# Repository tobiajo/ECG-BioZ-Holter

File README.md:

# ECG/BioZ Holter (c) by Tobias Johansson

Design and development of a pocket-sized ECG device with respiration monitoring, accelerometer and gyroscope. The produced prototype transmits sampled data with a MCU (PIC24) over Bluetooth to an Android device for which a simple app was developed. To achieve the objective; a system solution was engineered, components chose, PCB designed, soldering done and components programmed or configured.

## Main components

- Texas Instruments ADS1292R
- InvenSense MPU-6050
- Microchip PIC24FJ64GA002
- HC-05 Bluetooth Module

## System overview

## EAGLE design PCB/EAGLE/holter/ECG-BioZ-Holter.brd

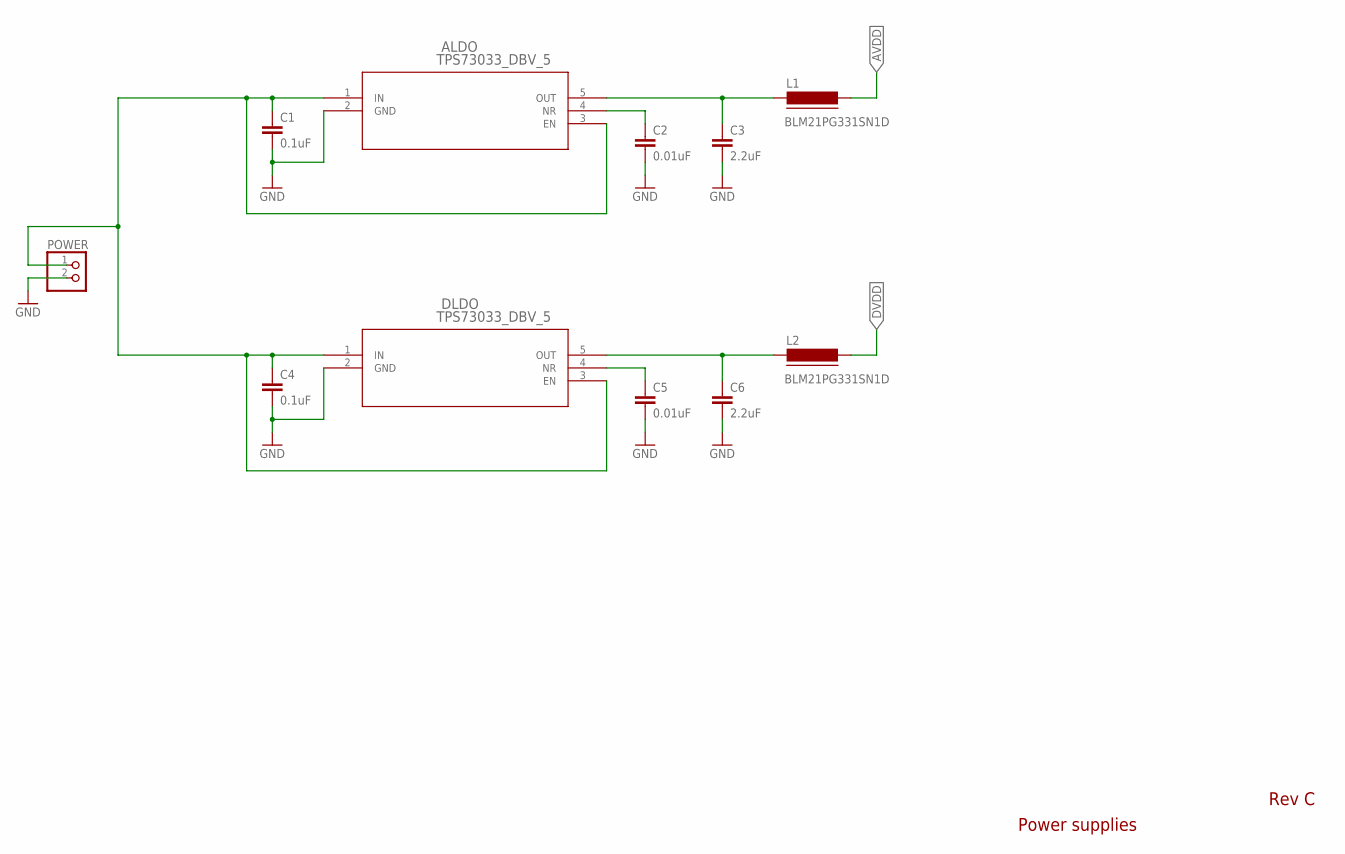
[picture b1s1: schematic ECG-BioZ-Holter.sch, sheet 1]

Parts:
ALDO: TPS73033_DBV_5; DBV5
C1, C4: 0.1uF; C0805
C2, C5: 0.01uF; C0805
C3, C6: 2.2uF; C0805
DLDO: TPS73033_DBV_5; DBV5
L1, L2: BLM21PG331SN1D; FB805
POWER: PINHD-1X2; 1X02

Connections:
AVDD: L1.2; also elsewhere on the board
DVDD: L2.2; also elsewhere on the board
GND: ALDO.2 (GND), C1.2, C2.2, C3.2, C4.2, C5.2, C6.2, DLDO.2 (GND), POWER.2; also elsewhere on the board
unnamed: ALDO.1 (IN), ALDO.3 (EN), C1.1, C4.1, DLDO.1 (IN), DLDO.3 (EN), POWER.1
unnamed: C5.1, DLDO.4 (NR)
unnamed: ALDO.4 (NR), C2.1
unnamed: ALDO.5 (OUT), C3.1, L1.1
unnamed: C6.1, DLDO.5 (OUT), L2.1

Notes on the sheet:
Rev C
Power supplies

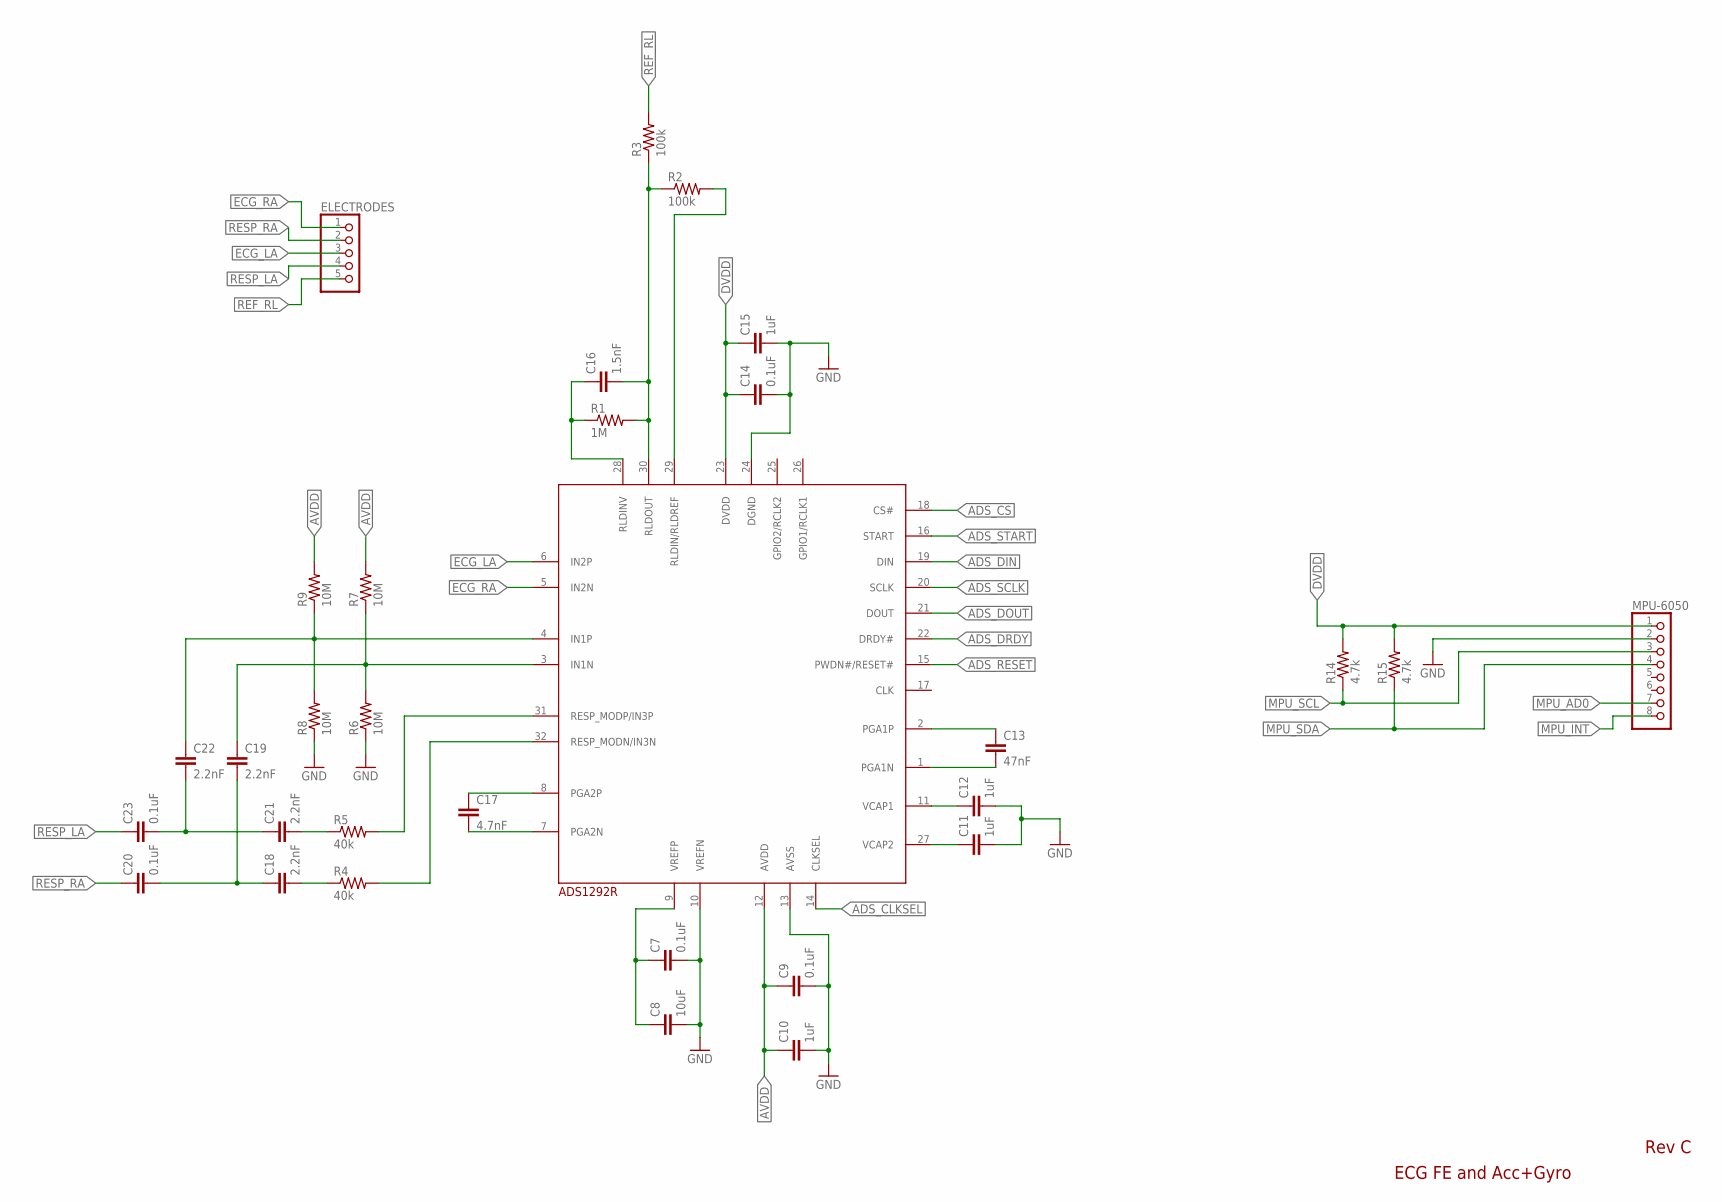
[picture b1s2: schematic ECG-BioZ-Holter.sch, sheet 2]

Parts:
ADS1292R: ADS1292R; TQFP-32
C7, C9, C14, C20, C23: 0.1uF; C0805
C8: 10uF; C0805
C10, C11, C12, C15: 1uF; C0805
C13: 47nF; C0805
C16: 1.5nF; C0805
C17: 4.7nF; C0805
C18, C19, C21, C22: 2.2nF; C0805
ELECTRODES: PINHD-1X5; 1X05
MPU: MPU-6050; 1X08
R1: 1M; R0805
R2, R3: 100k; R0805
R4, R5: 40k; R0805
R6, R7, R8, R9: 10M; R0805
R14, R15: 4.7k; R0805

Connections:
ADS_CLKSEL: ADS1292R.14 (CLKSEL); also elsewhere on the board
ADS_CS: ADS1292R.18 (CS#); also elsewhere on the board
ADS_DIN: ADS1292R.19 (DIN); also elsewhere on the board
ADS_DOUT: ADS1292R.21 (DOUT); also elsewhere on the board
ADS_DRDY: ADS1292R.22 (DRDY#); also elsewhere on the board
ADS_RESET: ADS1292R.15 (PWDN#/RESET#); also elsewhere on the board
ADS_SCLK: ADS1292R.20 (SCLK); also elsewhere on the board
ADS_START: ADS1292R.16 (START); also elsewhere on the board
AVDD: ADS1292R.12 (AVDD), C9.1, C10.1, R7.2, R9.2; also elsewhere on the board
DVDD: ADS1292R.23 (DVDD), C14.1, C15.1, MPU.1, R14.2, R15.2; also elsewhere on the board
ECG_LA: ADS1292R.6 (IN2P), ELECTRODES.3
ECG_RA: ADS1292R.5 (IN2N), ELECTRODES.1
GND: ADS1292R.10 (VREFN), ADS1292R.13 (AVSS), ADS1292R.24 (DGND), C7.2, C8.2, C9.2, C10.2, C11.2, C12.2, C14.2, C15.2, MPU.2, R6.1, R8.1; also elsewhere on the board
MPU_AD0: MPU.7; also elsewhere on the board
MPU_INT: MPU.8; also elsewhere on the board
MPU_SCL: MPU.3, R14.1; also elsewhere on the board
MPU_SDA: MPU.4, R15.1; also elsewhere on the board
unnamed: ADS1292R.11 (VCAP1), C12.1
unnamed: ADS1292R.9 (VREFP), C7.1, C8.1
unnamed: ADS1292R.27 (VCAP2), C11.1
unnamed: ADS1292R.2 (PGA1P), C13.1
unnamed: ADS1292R.1 (PGA1N), C13.2
unnamed: ADS1292R.30 (RLDOUT), C16.2, R1.2, R2.1, R3.1
unnamed: ADS1292R.28 (RLDINV), C16.1, R1.1
unnamed: ADS1292R.29 (RLDIN/RLDREF), R2.2
unnamed: ADS1292R.8 (PGA2P), C17.1
unnamed: ADS1292R.7 (PGA2N), C17.2
unnamed: ADS1292R.32 (RESP_MODN/IN3N), R4.2
unnamed: C18.2, R4.1
unnamed: C18.1, C19.2, C20.2
unnamed: ADS1292R.3 (IN1N), C19.1, R6.2, R7.1
unnamed: ADS1292R.31 (RESP_MODP/IN3P), R5.2
unnamed: C21.2, R5.1
unnamed: C21.1, C22.2, C23.2
unnamed: ADS1292R.4 (IN1P), C22.1, R8.2, R9.1
REF_RL: ELECTRODES.5, R3.2
RESP_LA: C23.1, ELECTRODES.4
RESP_RA: C20.1, ELECTRODES.2

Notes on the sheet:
Rev C
ECG FE and Acc+Gyro

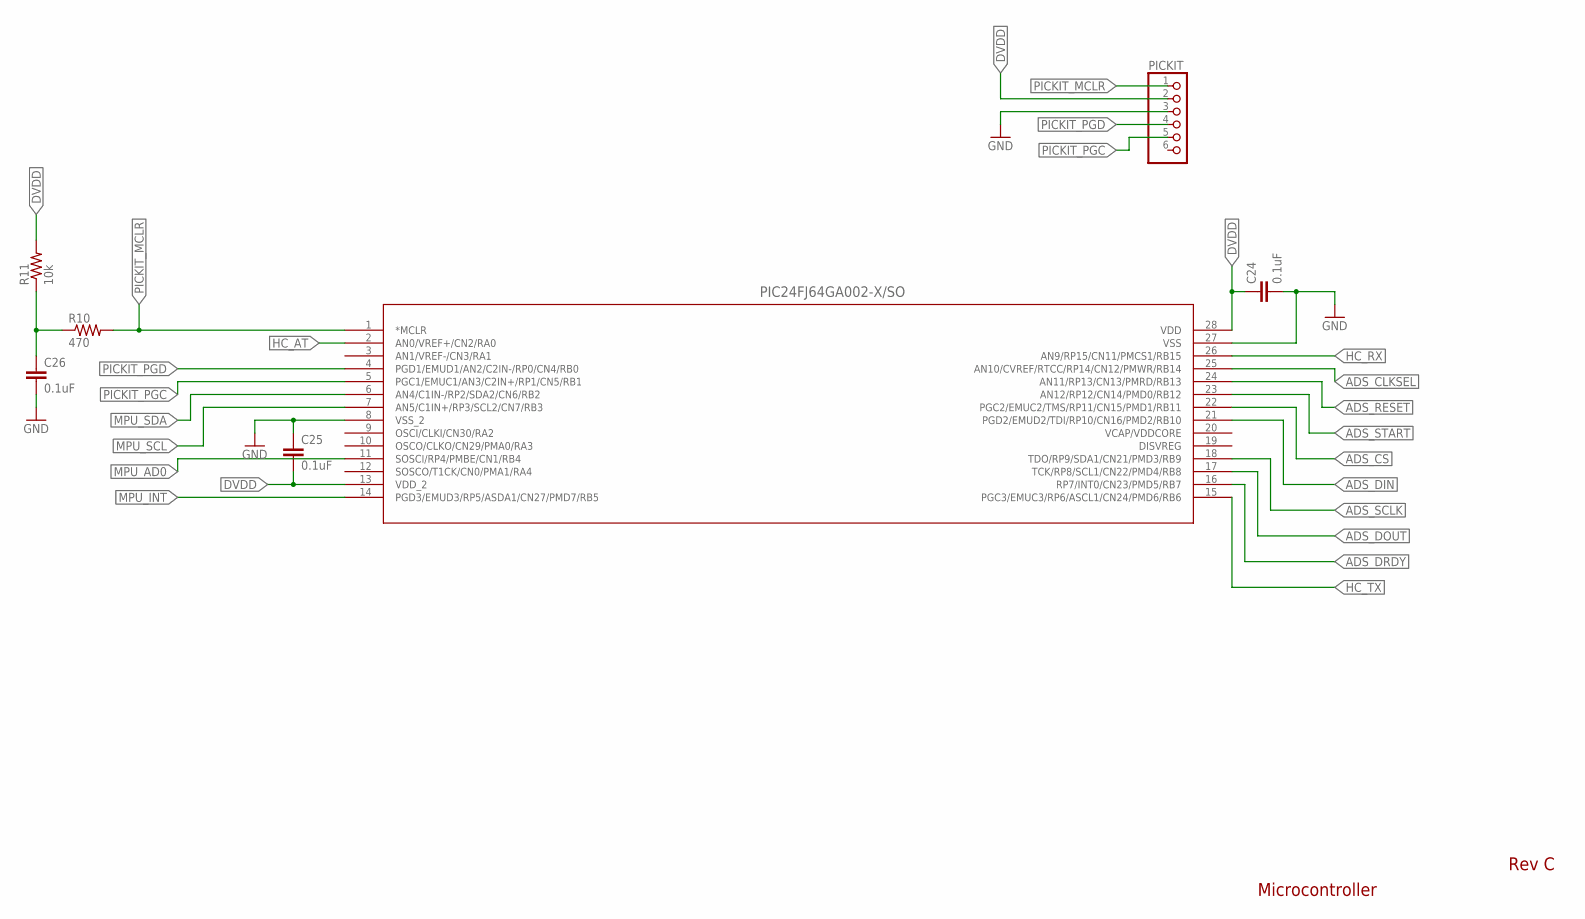
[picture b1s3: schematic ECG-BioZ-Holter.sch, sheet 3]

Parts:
C24, C25, C26: 0.1uF; C0805
PIC24F: PIC24FJ64GA002-X/SO; SOIC28-W_MC
PICKIT: PINHD-1X6; 1X06
R10: 470; R0805
R11: 10k; R0805

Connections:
ADS_CLKSEL: PIC24F.25 (AN10/CVREF/RTCC/RP14/CN12/PMWR/RB14); also elsewhere on the board
ADS_CS: PIC24F.22 (PGC2/EMUC2/TMS/RP11/CN15/PMD1/RB11); also elsewhere on the board
ADS_DIN: PIC24F.21 (PGD2/EMUD2/TDI/RP10/CN16/PMD2/RB10); also elsewhere on the board
ADS_DOUT: PIC24F.17 (TCK/RP8/SCL1/CN22/PMD4/RB8); also elsewhere on the board
ADS_DRDY: PIC24F.16 (RP7/INT0/CN23/PMD5/RB7); also elsewhere on the board
ADS_RESET: PIC24F.24 (AN11/RP13/CN13/PMRD/RB13); also elsewhere on the board
ADS_SCLK: PIC24F.18 (TDO/RP9/SDA1/CN21/PMD3/RB9); also elsewhere on the board
ADS_START: PIC24F.23 (AN12/RP12/CN14/PMD0/RB12); also elsewhere on the board
DVDD: C24.1, C25.2, PIC24F.13 (VDD_2), PIC24F.28 (VDD), PICKIT.2, R11.2; also elsewhere on the board
GND: C24.2, C25.1, C26.2, PIC24F.8 (VSS_2), PIC24F.27 (VSS), PICKIT.3; also elsewhere on the board
HC_AT: PIC24F.2 (AN0/VREF+/CN2/RA0); also elsewhere on the board
HC_RX: PIC24F.26 (AN9/RP15/CN11/PMCS1/RB15); also elsewhere on the board
HC_TX: PIC24F.15 (PGC3/EMUC3/RP6/ASCL1/CN24/PMD6/RB6); also elsewhere on the board
MPU_AD0: PIC24F.11 (SOSCI/RP4/PMBE/CN1/RB4); also elsewhere on the board
MPU_INT: PIC24F.14 (PGD3/EMUD3/RP5/ASDA1/CN27/PMD7/RB5); also elsewhere on the board
MPU_SCL: PIC24F.7 (AN5/C1IN+/RP3/SCL2/CN7/RB3); also elsewhere on the board
MPU_SDA: PIC24F.6 (AN4/C1IN-/RP2/SDA2/CN6/RB2); also elsewhere on the board
unnamed: C26.1, R10.1, R11.1
PICKIT_MCLR: PIC24F.1 (*MCLR), PICKIT.1, R10.2
PICKIT_PGC: PIC24F.5 (PGC1/EMUC1/AN3/C2IN+/RP1/CN5/RB1), PICKIT.5
PICKIT_PGD: PIC24F.4 (PGD1/EMUD1/AN2/C2IN-/RP0/CN4/RB0), PICKIT.4

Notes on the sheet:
Rev C
Microcontroller

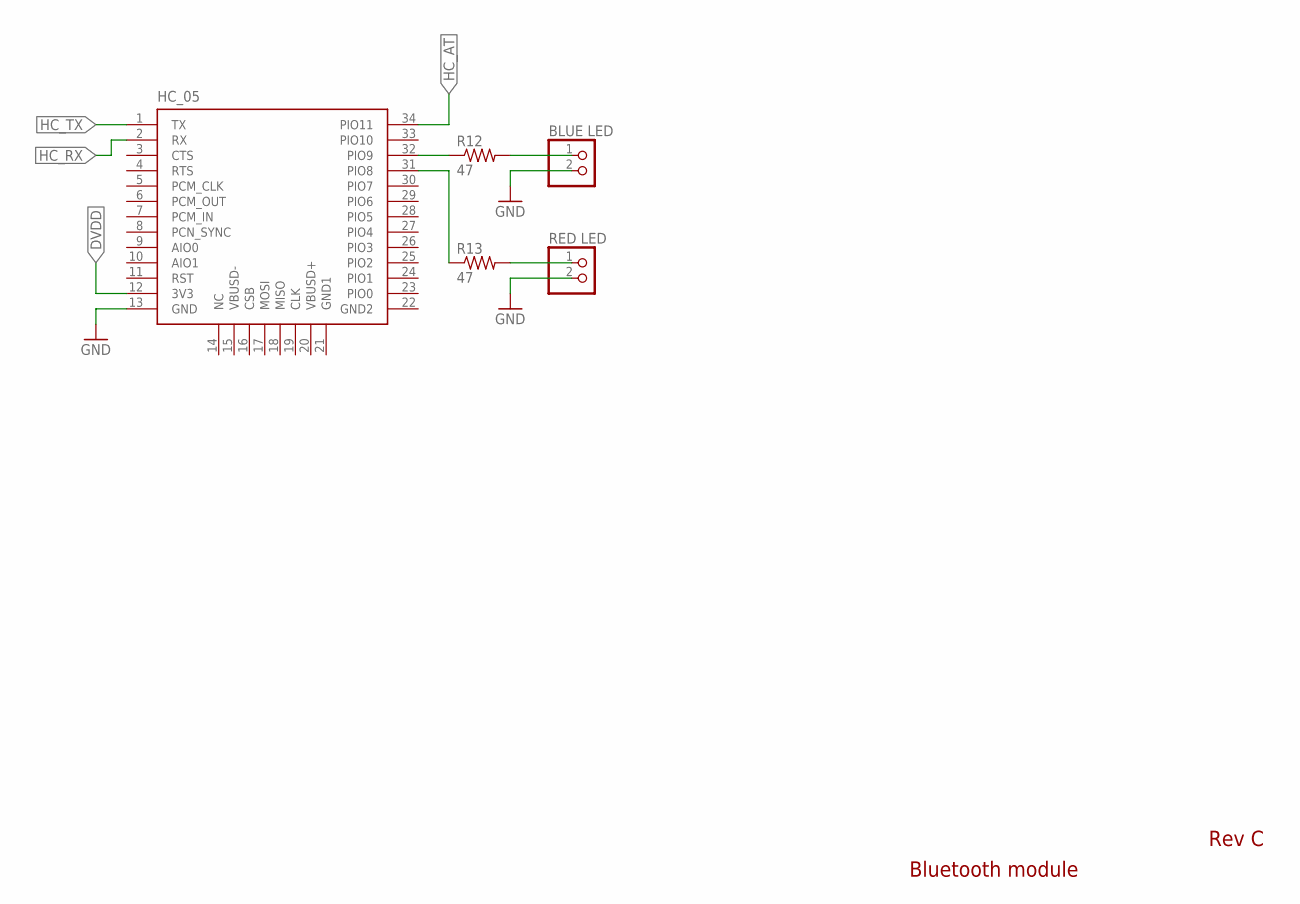
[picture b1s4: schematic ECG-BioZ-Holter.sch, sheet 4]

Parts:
BLUE: BLUE LED; 1X02
HC_05: HC_05; BLUETOOTH_SMD
R12, R13: 47; R0805
RED: RED LED; 1X02

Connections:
DVDD: HC_05.12 (3V3); also elsewhere on the board
GND: BLUE.2, HC_05.13 (GND), RED.2; also elsewhere on the board
HC_AT: HC_05.34 (PIO11); also elsewhere on the board
HC_RX: HC_05.2 (RX); also elsewhere on the board
HC_TX: HC_05.1 (TX); also elsewhere on the board
unnamed: HC_05.32 (PIO9), R12.1
unnamed: BLUE.1, R12.2
unnamed: HC_05.31 (PIO8), R13.1
unnamed: R13.2, RED.1

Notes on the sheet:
Rev C
Bluetooth module

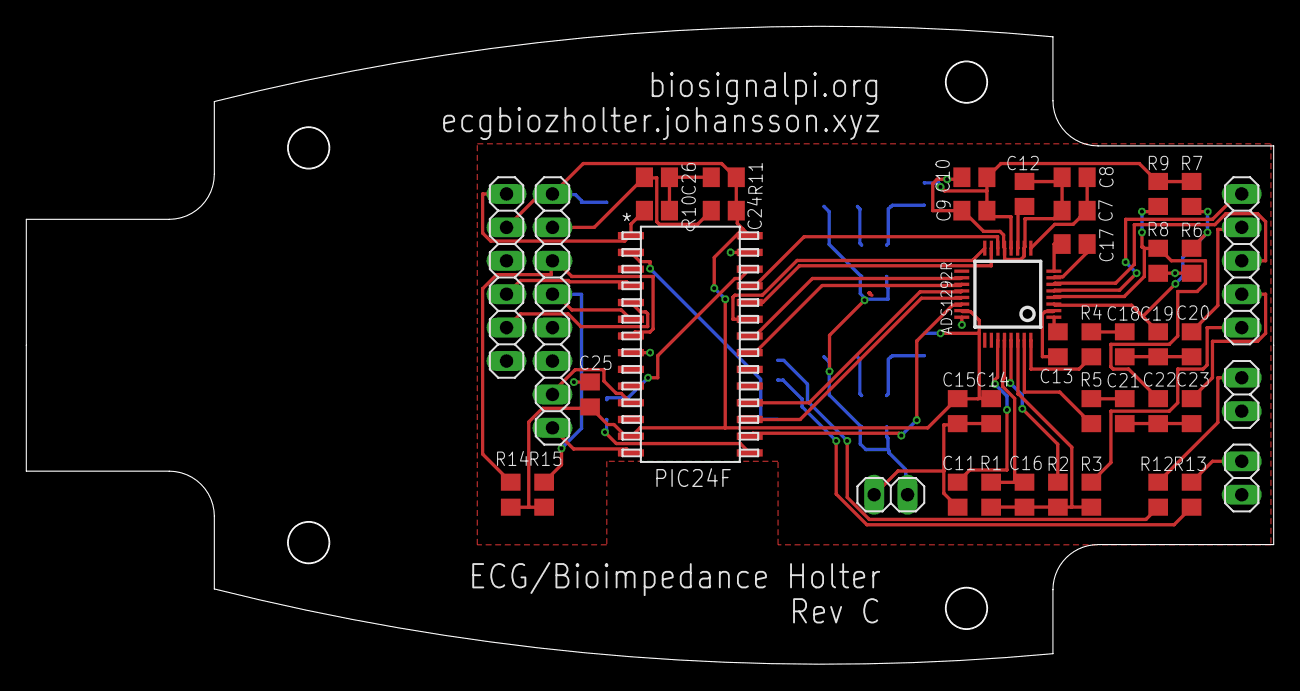
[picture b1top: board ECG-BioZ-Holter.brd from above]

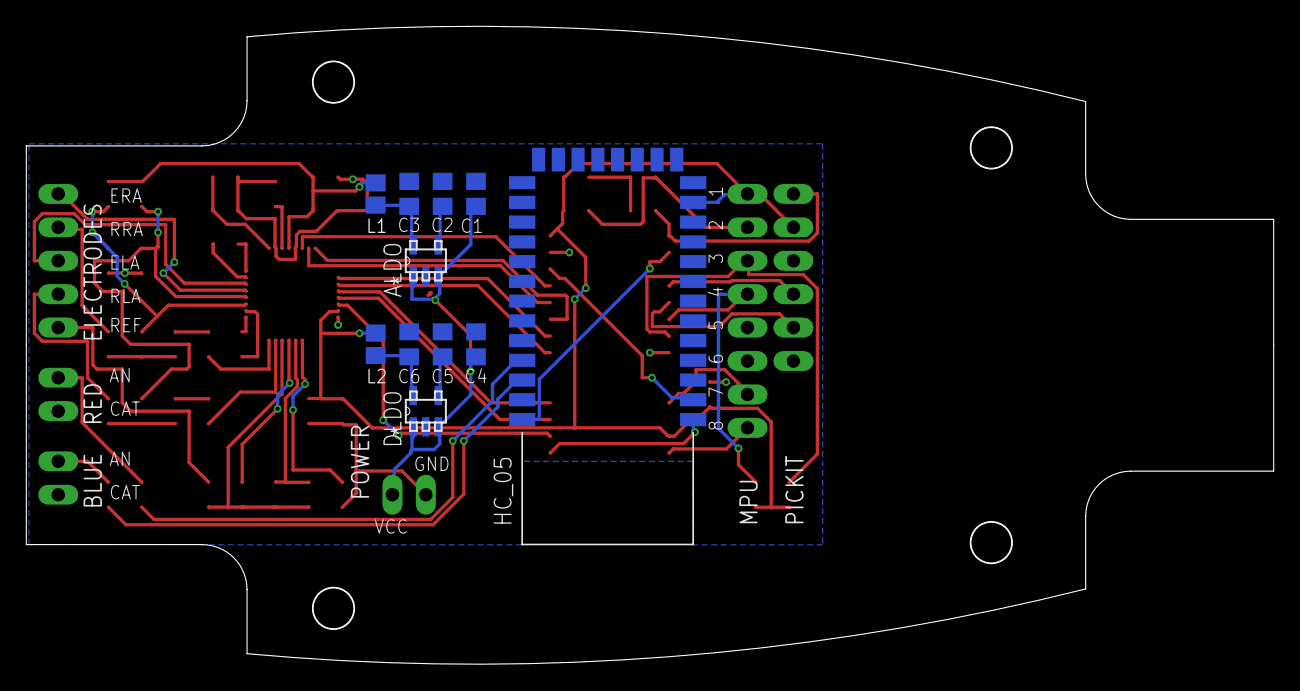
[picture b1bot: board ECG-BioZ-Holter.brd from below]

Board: 2 copper layers, 94.8 x 48.5 mm, 54 parts (11 on the bottom side), 54 nets.

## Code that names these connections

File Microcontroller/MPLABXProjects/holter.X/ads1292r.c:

/*
 * File:    ads1292r.c
 * Project: ecgbiozholter.johansson.xyz
 * MCU:     Microchip PIC24FJ64GA002
 * Author:  Tobias Johansson
 * Version: 1.3, 23 Apr 2015
 */

#include "ads1292r.h"

#define RIGHT_LEG_DRIVE 1 // set 1 for enable RLD, otherwise disabled

// Initialization.
void ads1292r_init(void) {
    // Pin directions
    TRISBbits.TRISB14 = 0; // ADS_CLKSEL = out
    TRISBbits.TRISB13 = 0; // ADS_RESET  = out
    TRISBbits.TRISB12 = 0; // ADS_START  = out
    TRISBbits.TRISB11 = 0; // ADS_CS     = out
    TRISBbits.TRISB7  = 1; // ADS_DRDY   = in

    // Power-Up Settings
    LATBbits.LATB14 = 1; // internal clock
    LATBbits.LATB13 = 1; // no: reset
    LATBbits.LATB12 = 1; // start
    LATBbits.LATB11 = 1; // no: chip select

    // PPS SPI2
    PPSInput (PPS_SDI2, PPS_RP8);     // ADS_DOUT
    PPSOutput(PPS_RP9,  PPS_SCK2OUT); // ADS_SCLK
    PPSOutput(PPS_RP10, PPS_SDO2);    // ADS_DIN

    // SPI2 init
    // "If SCLK is 1 MHz, one byte is transferred in 8 µs. Because this transfer
    // time exceeds the t_SDECODE specification, the processor can send
    // subsequent bytes without delay." - Data sheet p. 37
    SPI2CON1 = 0x003D; // Master Mode, SPI clock = 1000 kHz (Fcy = 16 MHz)
    SPI2STAT = 0x8000; // Enables module

    // Delay for Power-On Reset and Oscillator Start-Up
    __delay_ms(1000);

    // "The internal oscillator generates a 512-kHz clock." - Data sheet p. 16
    // "f_MOD = f_CLK / 4 (default, use when f_CLK = 512 kHz)" - Data sheet. 47
    // => t_MOD = 7.8125 us, t_CLK = 1.953125 us

    // Issue Reset Pulse then Wait for 18 t_CLKs
    LATBbits.LATB13 = 0;
    __delay_us(8);  // Reset low width min = 1 t_MOD
    LATBbits.LATB13 = 1;
    __delay_us(36); // Recommended wait after reset = 18 t_CLK
	
    // "After releasing RESET, the configuration register must be programmed..."
    // - Data sheet p. 62

    // Device Wakes Up in RDATAC Mode, so Send
    // SDATAC Command so Registers can be Written
    ads1292r_command(ADS1292R_CMD_SDATAC);

    ads1292r_config();

    // Activate Conversion
    LATBbits.LATB12 = 1; // START = 1

    // Put the Device Back in RDATAC Mode
    ads1292r_command(ADS1292R_CMD_RDATAC);
}

// Configuration settings.
void ads1292r_config(void) {
    // Continuous conversion, Data Rate = 1 kSPS
    ads1292r_wreg(ADS1292R_REG_CONFIG1, 0x03);

    // Reference buffer is enabled
    ads1292r_wreg(ADS1292R_REG_CONFIG2, 0xA0);

    // Channel 1 PGA gain = 4, Normal electrode input
    ads1292r_wreg(ADS1292R_REG_CH1SET, 0x40);

    // Channel 2 PGA gain = 4, Normal electrode input
    ads1292r_wreg(ADS1292R_REG_CH2SET, 0x40);

    // Chop frequency = f_MOD/16, RLD buffer is enabled if RIGHT_LEG_DRIVE == 1
    #if RIGHT_LEG_DRIVE == 1
    #define RLD_BIT 0x20
    #else
    #define RLD_BIT 0x00
    #endif
    ads1292r_wreg(ADS1292R_REG_RLD_SENS, 0x00 | RLD_BIT);

    // CLK_DIV bit of LOFF_STAT register = 0 by default

    // Enables respiration circuits, Respiration phase = 112.5°
    // "It can be noted that gain = 4 and phase = 112.5° yield the best
    // performance..." - Data sheet p. 59
    ads1292r_wreg(ADS1292R_REG_RESP1, 0xEA);

    // Resp frequency, 32 kHz, RLDREF signal (AVDD-AVSS)/2 generated internally
    ads1292r_wreg(ADS1292R_REG_RESP2, 0x03);
}

//------------------------------------------------------------------------------
// Basic Functions

// Transfer data bidirectional.
UINT8 ads1292r_transfer(UINT8 data) {
    SPI2BUF = data;               // write to buffer
    while (!SPI2STATbits.SPIRBF); // wait transfer
    return SPI2BUF;               // read received
}

// Set chip select low.
void ads1292r_cs_low(void) {
    LATBbits.LATB11 = 0;
}

// Set chip select high.
void ads1292r_cs_high(void) {
    // "Always wait four or more t_CLK cycles before taking CS high."
    // - Data sheet p. 28
    __delay_us(8);
    LATBbits.LATB11 = 1;
}

//------------------------------------------------------------------------------
// Putting it Together

// Sends a command.
void ads1292r_command(UINT8 cmd) {
    ads1292r_cs_low();
    ads1292r_transfer(cmd);
    ads1292r_cs_high();
}

// Reads from a register.
UINT8 ads1292r_rreg(UINT8 reg) {
    UINT8 value;
    ads1292r_cs_low();

    ads1292r_transfer(ADS1292R_CMD_RREG | reg);
    ads1292r_transfer(0x00); // [number of registers to be read]-1 = 0x00
    value = ads1292r_transfer(ADS1292R_CMD_DUMMY);

    ads1292r_cs_high();
    return value;
}

// Writes to a register.
void ads1292r_wreg(UINT8 reg, UINT8 value) {
    ads1292r_cs_low();

    ads1292r_transfer(ADS1292R_CMD_WREG | reg);
    ads1292r_transfer(0x00); // [number of registers to be written]-1 = 0x00
    ads1292r_transfer(value);

    ads1292r_cs_high();
}

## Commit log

2015-05-17 Add licence
2015-05-17 Add Android application
2015-05-17 Add PIC24F program
2015-05-17 Add HC-05 AT terminal
2015-05-17 Add schematics
2015-10-13 Add prototype pictures
2015-10-13 Change pictures
2015-10-13 Move picture
2015-10-13 Change name on output plots
